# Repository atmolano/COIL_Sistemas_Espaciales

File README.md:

# COIL_Sistemas_Espaciales

Repositorio para el desarrollo y diseño del proyecto CubeSat. Este repositorio incluye código, esquemáticos, modelos 3D y otros archivos relacionados con el diseño y funcionamiento de los sistemas del proyecto.

## Estructura del Repositorio

El repositorio está organizado de la siguiente manera:

### Directorios principales

- **Códigos/Funcional**: Contiene el código fuente para el funcionamiento de los diferentes módulos y sensores utilizados en el proyecto, como BMP_280, GPS_NEO, GY_271, entre otros.

- **Diseño**: Incluye los archivos relacionados con el diseño físico y electrónico del sistema.
  - **3D**: Modelos tridimensionales de los componentes y ensamblajes del sistema.
  - **Esquemáticos**: Diagramas de circuitos electrónicos necesarios para el ensamblaje del sistema.
  - **Hiles**: Archivos de soporte y librerías.
  - **brd**: Archivos de diseño de PCB (circuito impreso) para la fabricación.

## Descripción de los Componentes

A continuación se listan los componentes principales integrados en el proyecto:

- **BMP_280**: Sensor de presión y temperatura.
- **GPS_NEO**: Módulo de GPS para geolocalización.
- **GY_271**: Sensor de campo magnético (brújula digital).
- **GY_271-MTQ**: Modificación del GY_271 para la integración con los magnetotorques.
- **MAGNETORQUERS**: Magnetotorques para el control de actitud mediante el uso de campos magnéticos.
- **MPU_6050**: Acelerómetro y giroscopio para la detección de movimiento y orientación.
- **SD_CARD**: Módulo de almacenamiento mediante tarjeta SD.

## Instalación y Uso

1. Clona este repositorio en tu máquina local:
   ```bash
   git clone https://github.com/tu_usuario/COIL_Sistemas_Espaciales.git
   ```
2. Accede al directorio principal del proyecto:
   ```bash
   cd COIL_Sistemas_Espaciales
   ```
3. Abre la carpeta `Códigos/Funcional` para acceder al código fuente o la carpeta `Diseño` para los diseños físicos y electrónicos.

## Contribución

Si deseas contribuir al proyecto, por favor sigue estos pasos:

1. Haz un fork del repositorio.
2. Crea una nueva rama para tu función o corrección de errores (`git checkout -b feature/nueva-funcion`).
3. Realiza tus cambios y haz commit de ellos (`git commit -am 'Agrega nueva función'`).
4. Sube tus cambios al repositorio (`git push origin feature/nueva-funcion`).
5. Abre un pull request en GitHub.

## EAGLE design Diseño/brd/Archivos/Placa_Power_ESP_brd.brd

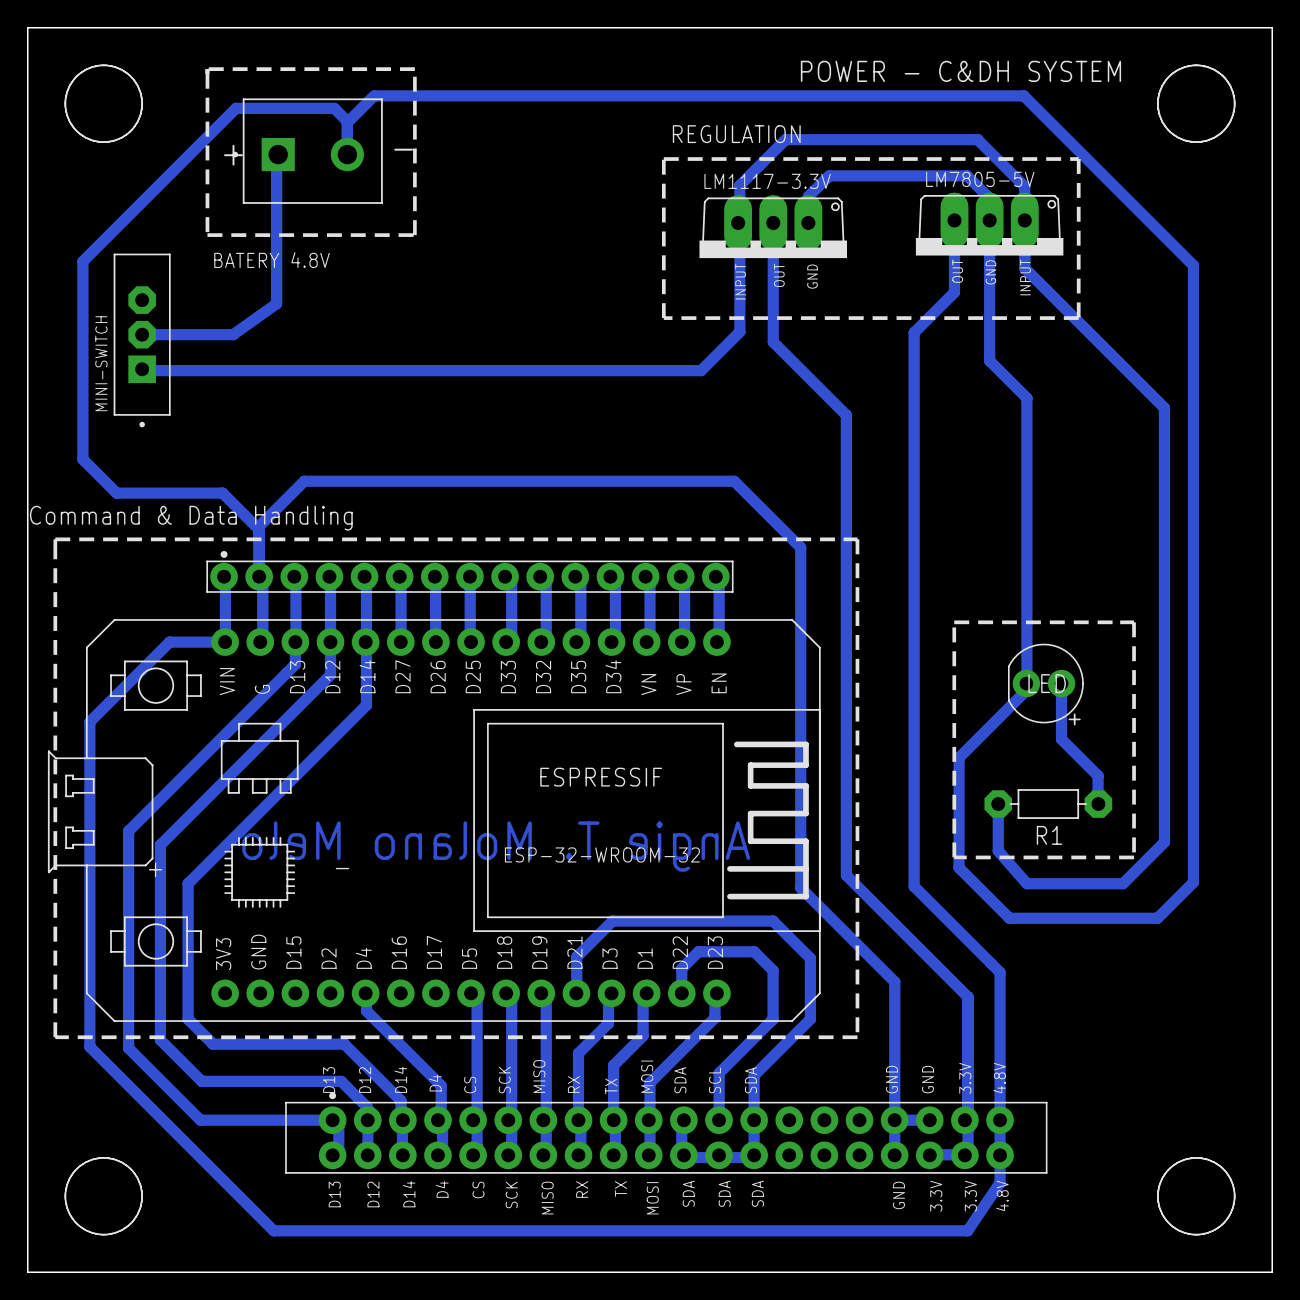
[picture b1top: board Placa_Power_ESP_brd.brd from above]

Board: 2 copper layers, 90.0 x 90.0 mm, 9 parts (0 on the bottom side), 28 nets.

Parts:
D1: LED; LEDRD254W60D565H860B_Y
ESP32DEVKIT: ESP32DEVKITV1SHRIDATTDUDHAT; ESP32-DEVKITV1
IC2: LM7805-5V; TO220V
J1: BATERY 4.8V; HANDSON_KF301-2P
LM1117-3.3V: LM1117-3.3; TO220V
MINI-SWITCH: MINI-SPDT-SW; SW_MINI-SPDT-SW-BACKUP
R1: RESAD724W46L381D178B
U$1: PIN_1X15
U$3: PINHEADER

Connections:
3.3V: LM1117-3.3V.2, U$3.19, U$3.22, U$3.23
4.8+: J1.1, MINI-SWITCH.2
4.8V: ESP32DEVKIT.VIN, IC2.3, U$1.1, U$3.20, U$3.21
CS: ESP32DEVKIT.D5, U$3.5, U$3.36
D4: ESP32DEVKIT.D4, U$3.4, U$3.37
D12: ESP32DEVKIT.D12, U$1.4, U$3.2, U$3.39
D13: ESP32DEVKIT.D13, U$1.3, U$3.1, U$3.40
D14: ESP32DEVKIT.D14, U$1.5, U$3.3, U$3.38
GND: D1.C, ESP32DEVKIT.GND, IC2.2, J1.2, LM1117-3.3V.1, U$1.2, U$3.17, U$3.18, U$3.24
MISO: ESP32DEVKIT.D19, U$3.7, U$3.34
MOSI: ESP32DEVKIT.D23, U$3.10, U$3.31
unnamed: D1.A, R1.2
unnamed: ESP32DEVKIT.EN, U$1.15
unnamed: ESP32DEVKIT.VP, U$1.14
unnamed: ESP32DEVKIT.VN, U$1.13
unnamed: ESP32DEVKIT.D34, U$1.12
unnamed: ESP32DEVKIT.D35, U$1.11
unnamed: ESP32DEVKIT.D32, U$1.10
unnamed: ESP32DEVKIT.D33, U$1.9
unnamed: ESP32DEVKIT.D25, U$1.8
unnamed: ESP32DEVKIT.D26, U$1.7
unnamed: ESP32DEVKIT.D27, U$1.6
unnamed: IC2.1, LM1117-3.3V.3, MINI-SWITCH.1, R1.1
RX: ESP32DEVKIT.D3, U$3.8, U$3.33
SCK: ESP32DEVKIT.D18, U$3.6, U$3.35
SCL: ESP32DEVKIT.D22, U$3.12
SDA: ESP32DEVKIT.D21, U$3.11, U$3.13, U$3.28, U$3.29, U$3.30
TX: ESP32DEVKIT.D1, U$3.9, U$3.32

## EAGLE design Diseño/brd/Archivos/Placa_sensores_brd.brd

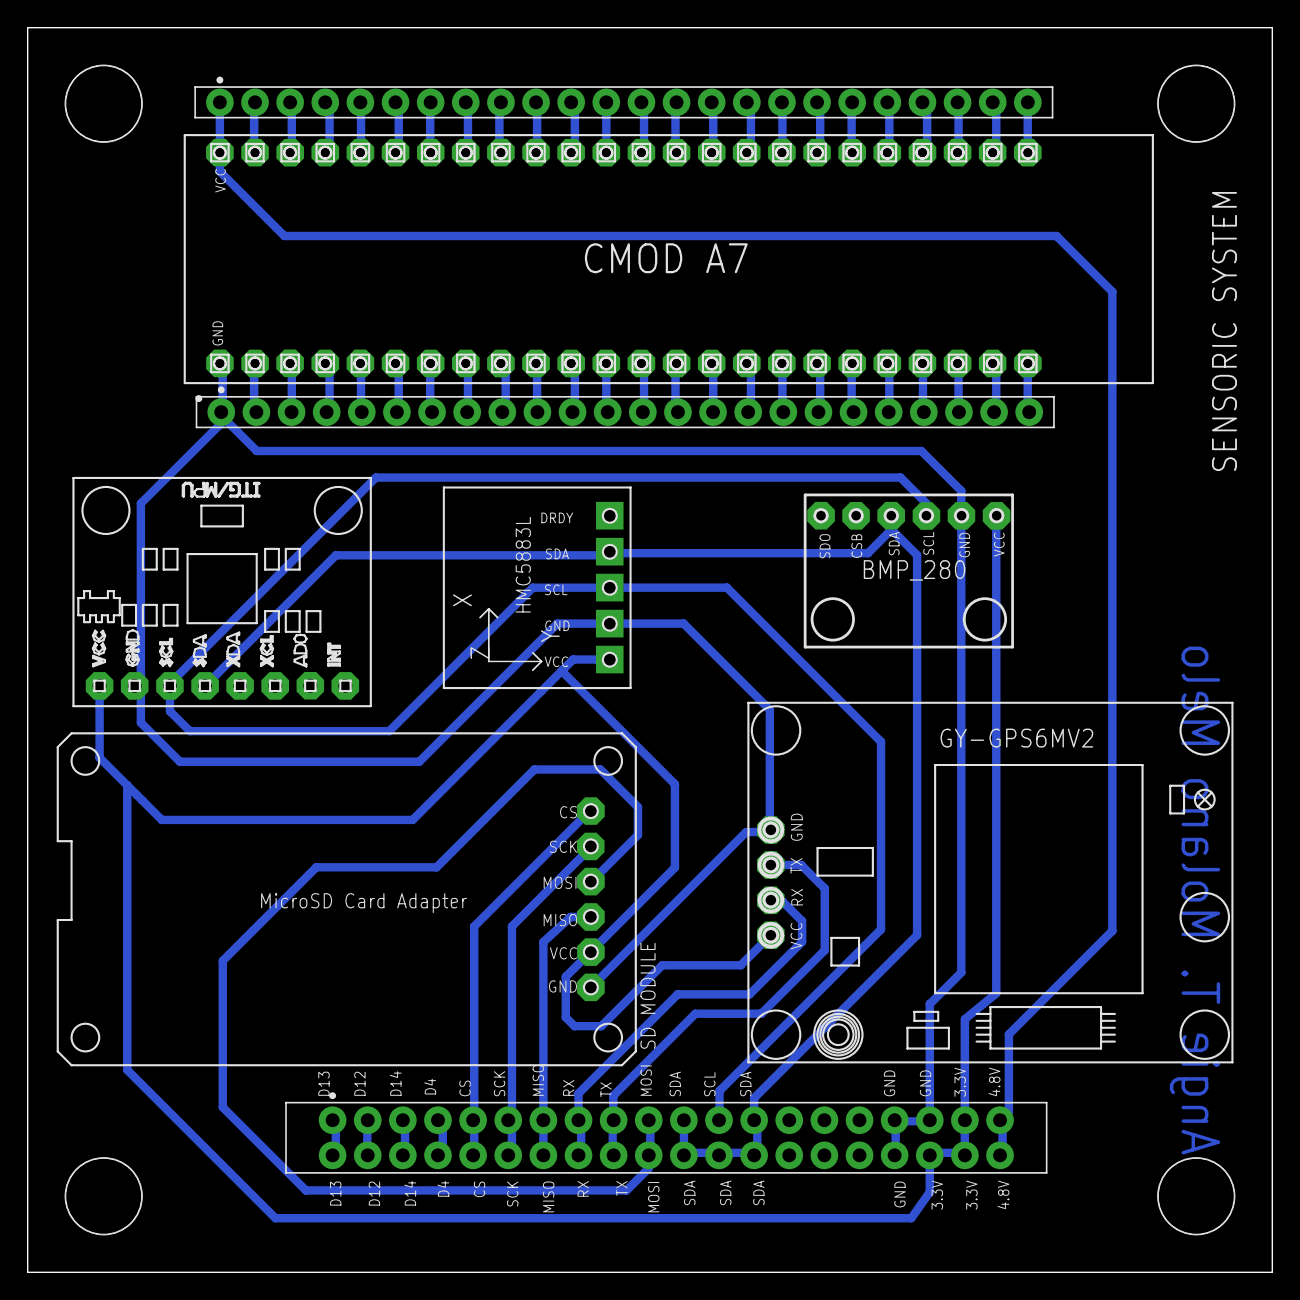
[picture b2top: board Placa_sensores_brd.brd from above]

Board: 2 copper layers, 90.0 x 90.0 mm, 9 parts (0 on the bottom side), 61 nets.

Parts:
CMOD: CMOD-A7
U1: GY-521
U2: HMC5883L; GY-271
U$1: GY-BPM280; GY-BMP280-FOOTPRINT
U$2: GPS-NEO-6M
U$3: PINHEADER
U$4: SD_MODULE
U$5, U$6: PIN1X24; PIN_1X24

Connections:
3.3V: U1.VCC, U2.VCC, U$1.VCC, U$2.P$1, U$3.19, U$3.22, U$3.23, U$4.VCC
4.8V: CMOD.48, U$3.20, U$3.21, U$5.1
CS: U$3.5, U$3.36, U$4.CS
D4: U$3.4, U$3.37
D12: U$3.2, U$3.39
D13: U$3.1, U$3.40
D14: U$3.3, U$3.38
GND: CMOD.1, U1.GND, U2.GND, U$1.GND, U$2.P$4, U$3.17, U$3.18, U$3.24, U$4.GND, U$6.1
MISO: U$3.7, U$3.34, U$4.MISO
MOSI: U$3.10, U$3.31, U$4.MOSI
unnamed: CMOD.47, U$5.2
unnamed: CMOD.46, U$5.3
unnamed: CMOD.45, U$5.4
unnamed: CMOD.44, U$5.5
unnamed: CMOD.43, U$5.6
unnamed: CMOD.42, U$5.7
unnamed: CMOD.41, U$5.8
unnamed: CMOD.27, U$5.22
unnamed: CMOD.40, U$5.9
unnamed: CMOD.39, U$5.10
unnamed: CMOD.26, U$5.23
unnamed: CMOD.38, U$5.11
unnamed: CMOD.37, U$5.12
unnamed: CMOD.36, U$5.13
unnamed: CMOD.35, U$5.14
unnamed: CMOD.34, U$5.15
unnamed: CMOD.33, U$5.16
unnamed: CMOD.32, U$5.17
unnamed: CMOD.31, U$5.18
unnamed: CMOD.30, U$5.19
unnamed: CMOD.29, U$5.20
unnamed: CMOD.28, U$5.21
unnamed: CMOD.25, U$5.24
unnamed: CMOD.2, U$6.2
unnamed: CMOD.3, U$6.3
unnamed: CMOD.4, U$6.4
unnamed: CMOD.5, U$6.5
unnamed: CMOD.6, U$6.6
unnamed: CMOD.7, U$6.7
unnamed: CMOD.24, U$6.24
unnamed: CMOD.23, U$6.23
unnamed: CMOD.22, U$6.22
unnamed: CMOD.21, U$6.21
unnamed: CMOD.20, U$6.20
unnamed: CMOD.19, U$6.19
unnamed: CMOD.18, U$6.18
unnamed: CMOD.17, U$6.17
unnamed: CMOD.16, U$6.16
unnamed: CMOD.15, U$6.15
unnamed: CMOD.14, U$6.14
unnamed: CMOD.13, U$6.13
unnamed: CMOD.12, U$6.12
unnamed: CMOD.11, U$6.11
unnamed: CMOD.10, U$6.10
unnamed: CMOD.9, U$6.9
unnamed: CMOD.8, U$6.8
RX: U$2.P$2, U$3.8, U$3.33
SCK: U$3.6, U$3.35, U$4.SCK
SCL: U1.SCL, U2.SCL, U$1.SCK, U$3.12
SDA: U1.SDA, U2.SDA, U$1.SDI, U$3.11, U$3.13, U$3.28, U$3.29, U$3.30
TX: U$2.P$3, U$3.9, U$3.32

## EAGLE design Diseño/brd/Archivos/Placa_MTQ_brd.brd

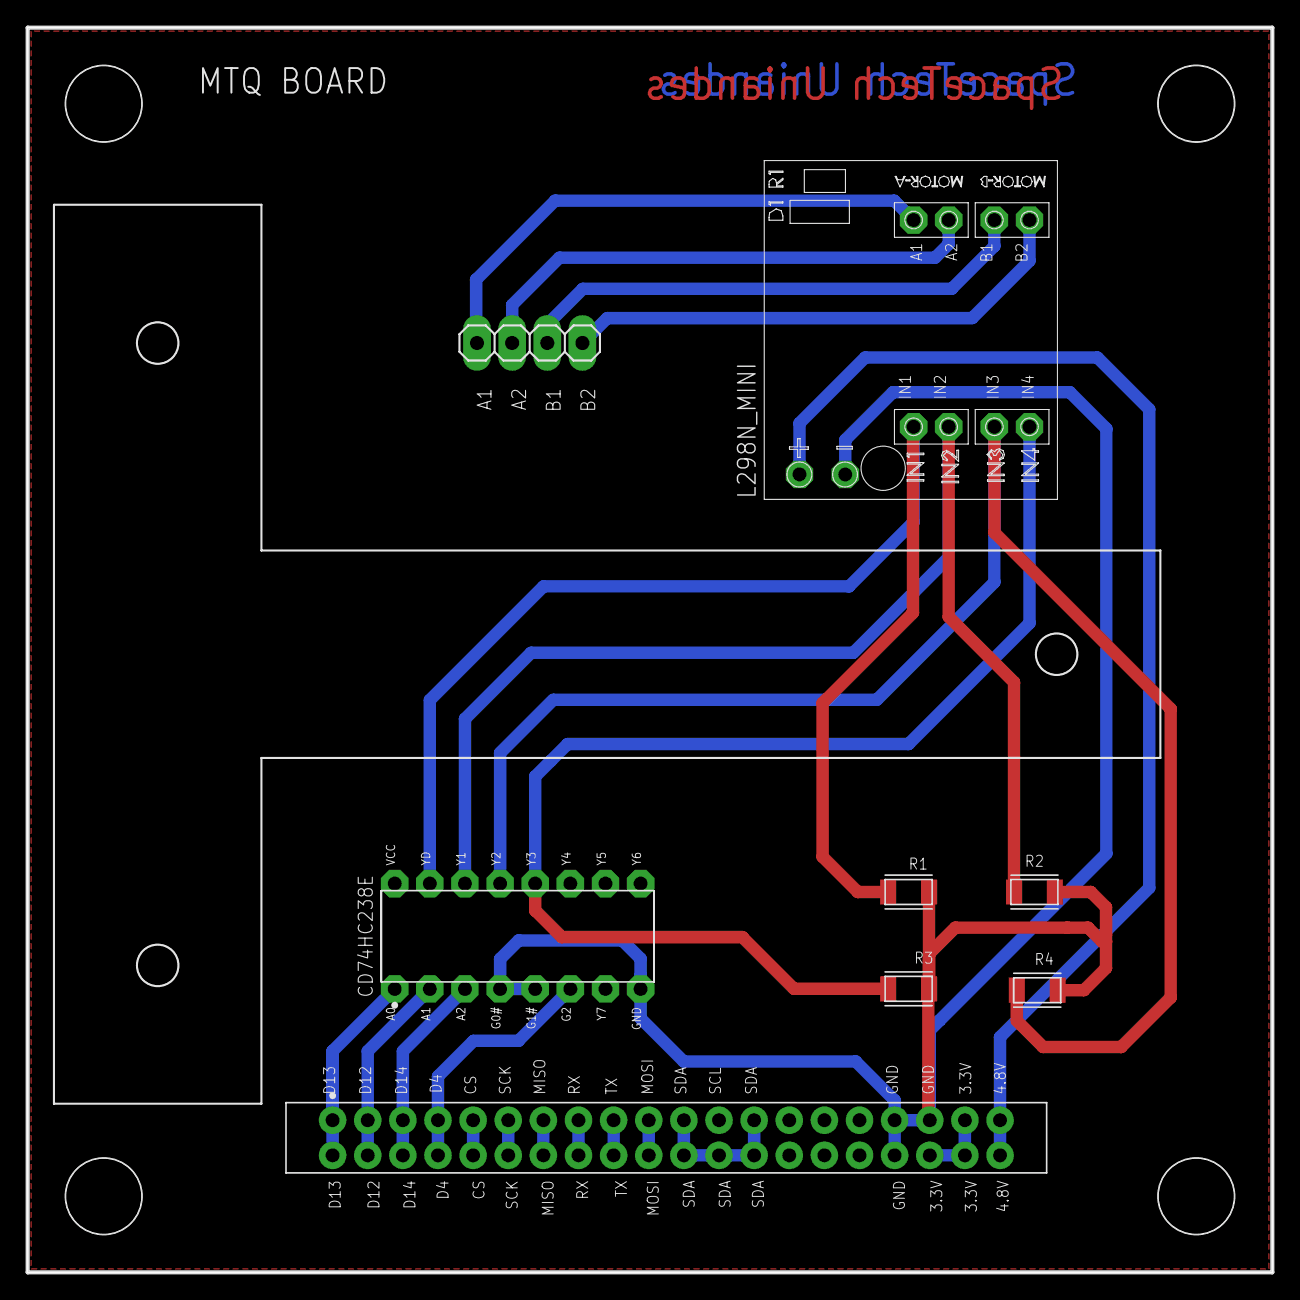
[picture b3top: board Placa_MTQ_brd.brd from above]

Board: 2 copper layers, 90.0 x 90.0 mm, 9 parts (0 on the bottom side), 22 nets.

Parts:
JP1: PINHD-1X4; 1X04
R1, R2, R3, R4: RES_SMD
U$1: CD74HC238E
U$2: L298N_MINI
U$3: PINHEADER
U$8: CASE_MTQ

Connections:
3.3V: U$3.19, U$3.22, U$3.23
4.8V: U$2.VCC, U$3.20, U$3.21
CS: U$3.5, U$3.36
D4: U$1.6, U$3.4, U$3.37
D12: U$1.2, U$3.2, U$3.39
D13: U$1.1, U$3.1, U$3.40
D14: U$1.3, U$3.3, U$3.38
GND: R1.2, R2.2, R3.2, R4.2, U$1.4, U$1.5, U$1.8, U$2.GND, U$3.17, U$3.18, U$3.24
MISO: U$3.7, U$3.34
MOSI: U$3.10, U$3.31
unnamed: R1.1, U$1.15, U$2.IN1
unnamed: R4.1, U$1.13, U$2.IN3
unnamed: R2.1, U$1.14, U$2.IN2
unnamed: R3.1, U$1.12, U$2.IN4
unnamed: JP1.1, U$2.A1
unnamed: JP1.2, U$2.A2
unnamed: JP1.3, U$2.B1
unnamed: JP1.4, U$2.B2
RX: U$3.8, U$3.33
SCK: U$3.6, U$3.35
SDA: U$3.11, U$3.13, U$3.28, U$3.29, U$3.30
TX: U$3.9, U$3.32

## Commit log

2024-10-27 Create BMP_280
2024-10-27 Create MPU_6050
2024-10-27 Create SD_CARD
2024-10-27 Create GPS_NEO
2024-10-27 Create MAGNETORQUERS
2024-10-27 Create GY_271
2024-10-27 Create GY_271-MTQ
2024-11-07 Create nn
    Diagrama de bloques Hiles, Imagenes y archivo
2024-11-07 Create d
2024-11-07 Create nn
2024-11-07 Create sa
2024-11-07 Create km
2024-11-07 Create s
2024-11-07 Create dfs
2024-11-07 Rename Actuators (1).png to Actuators.png
2024-11-07 Rename CubeSat (2).png to CubeSat.png
2024-11-08 Create f
2024-11-08 Create v
